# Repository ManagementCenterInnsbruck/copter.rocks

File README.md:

# copter.rocks
Quadcopter Design Contest by MCI &amp; Infineon
This software and hardware is hosted by a cooperation by MCI and Infineon for the "copter.rocks" quadcopter design contest in Austria

More information about the project: https://copter.rocks/

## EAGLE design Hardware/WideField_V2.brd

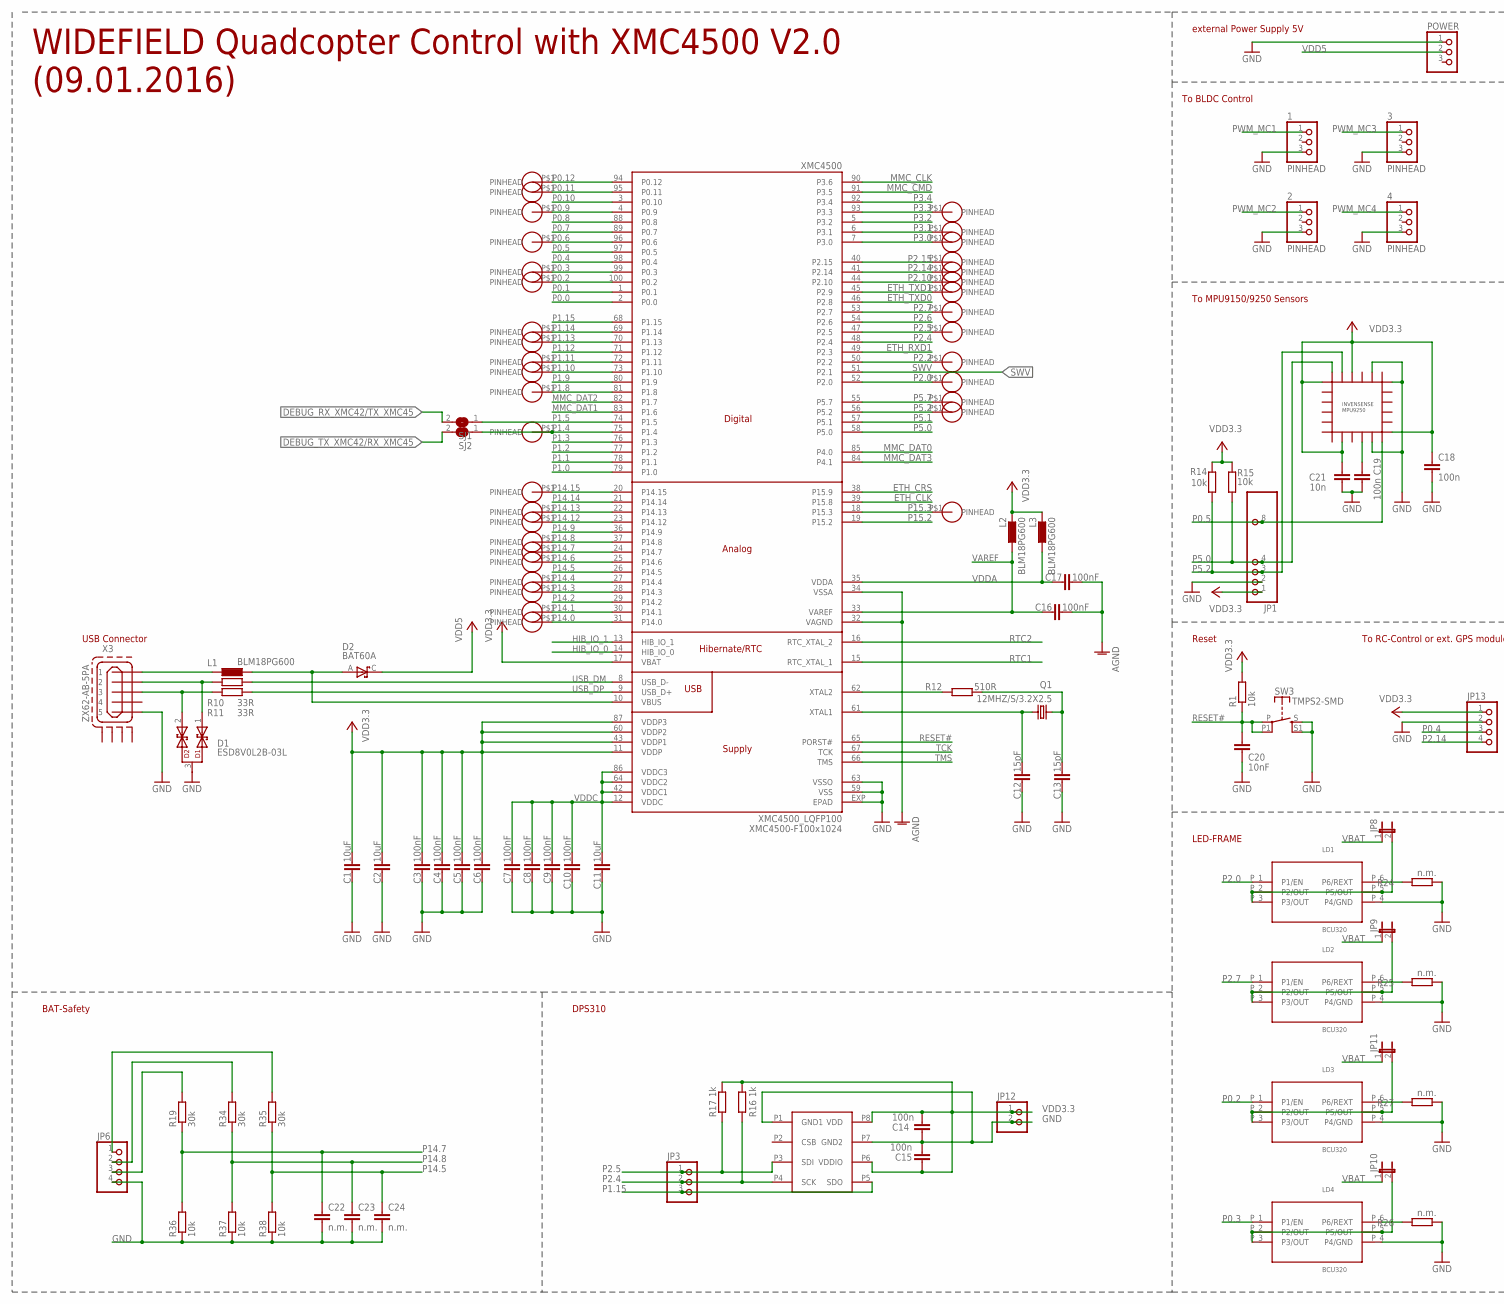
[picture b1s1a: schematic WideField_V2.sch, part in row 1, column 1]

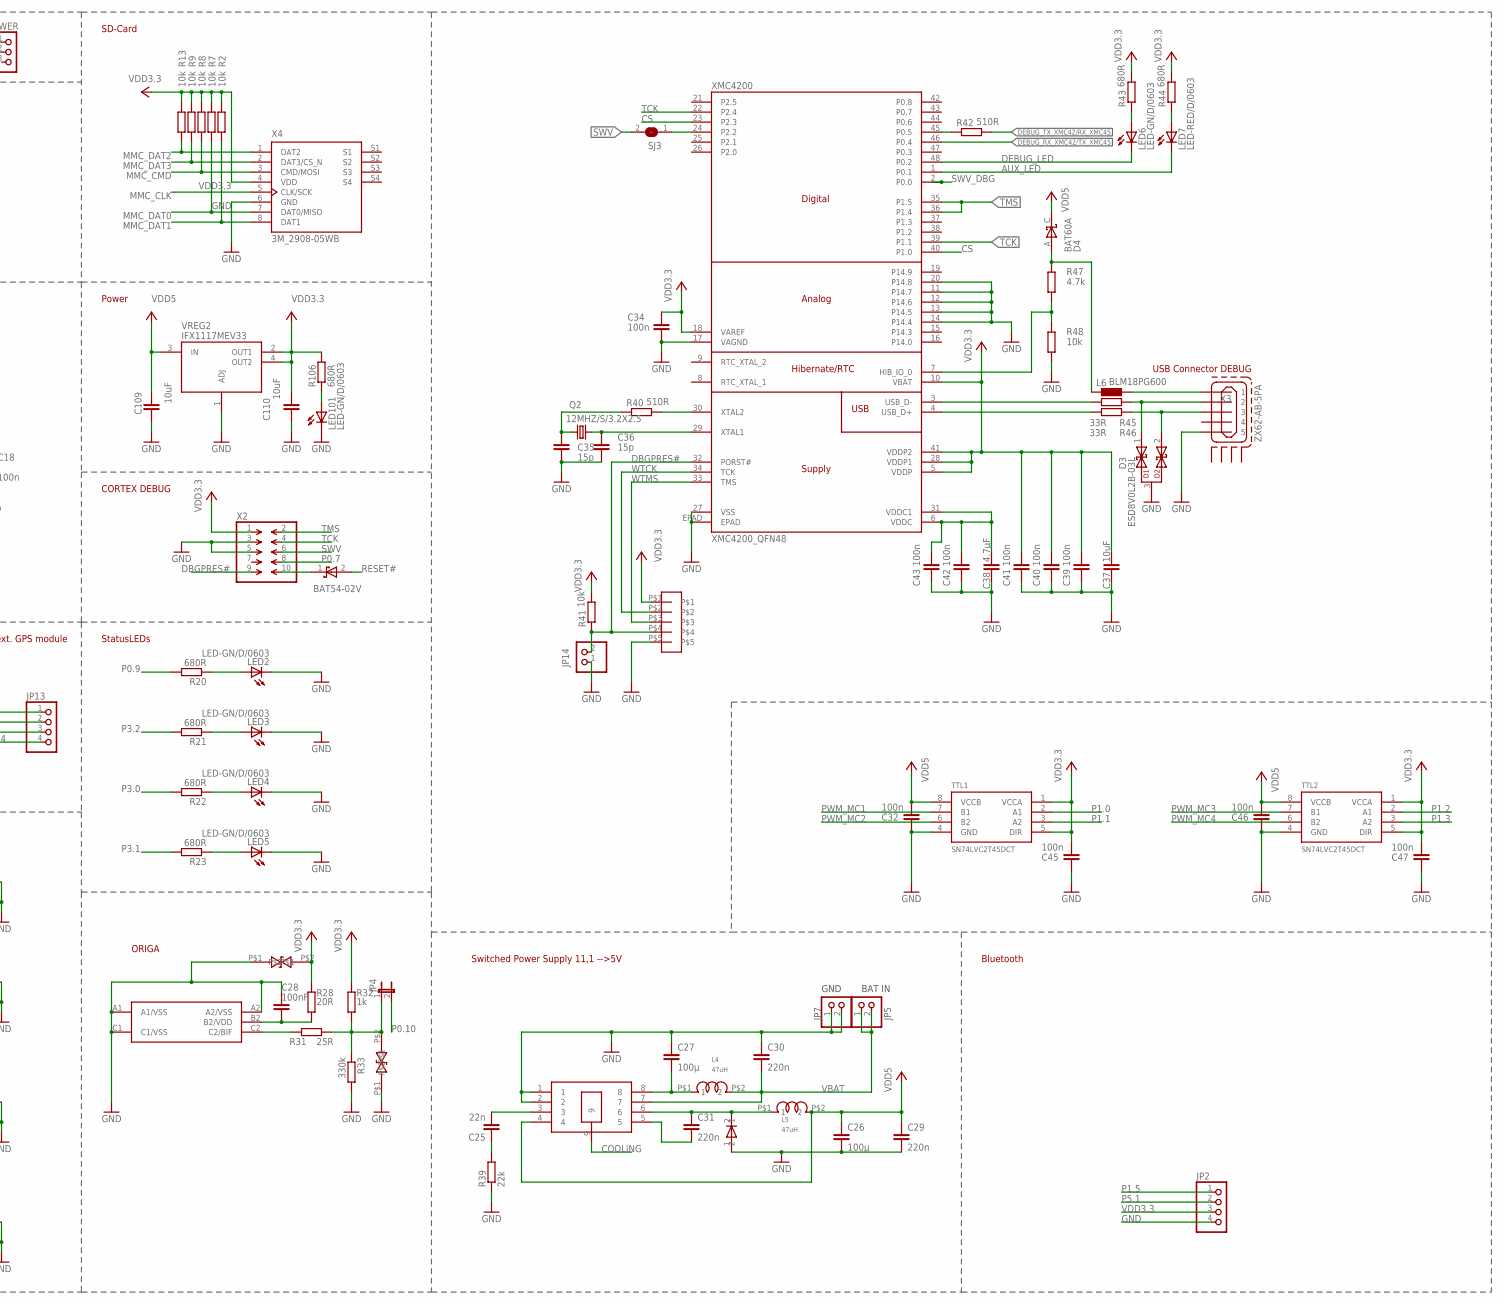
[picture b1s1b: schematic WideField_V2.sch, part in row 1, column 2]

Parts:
1, 2, 3, 4: PINHEAD; 1X03
C1, C2, C11, C37, C109, C110: 10uF; C0805K
C3, C4, C5, C6, C7, C8, C9, C10, C16, C17: 100nF; C0402
C12, C13: 15pF; C0402
C14, C15, C18, C19, C32, C45, C46, C47: 100n; C0603
C20: 10nF; C0603
C21: 10n; C0603
C22, C23, C24: n.m.; C0603K
C25: 22n; C0603
C26, C27: 100µ; C1210K
C28: 100nF; C0603
C29, C30, C31: 220n; C0603K
C34, C39, C40, C41, C42, C43: 100n; C0402
C35, C36: 15p; C0402
C38: 4.7µF; C0805K
D1, D3: ESD8V0L2B-03L; TSLP-3-1
D2, D4: BAT60A; SOD323-R
D5: INF-SOD323_V_1; INF-SOD323_V_1PRIMARY
D6, D7: ESD218-B1-02EL; TSLP-2-20
D8: BAT54-02V; SC79
DPS310: DPS310; LGA8R125P0X4_500X300X120
JP1: PINHD-1X10; 1X10
JP2, JP6, JP13: PINHD-1X4; 1X04
JP3: PINHD-1X3; 1X03
JP4, JP8, JP9, JP10, JP11: JP1E; JP1
JP5, JP7, JP12, JP14: PINHD-1X2; 1X02
L1, L2, L3, L6: BLM18PG600; L1608
L4, L5: 47uH; WE-TPC
LD1, LD2, LD3, LD4: BCU320; SC74
LED2, LED3, LED4, LED5, LED6, LED101: LED-GN/D/0603; CHIPLED_0603
LED7: LED-RED/D/0603; CHIPLED_0603
MPU9250: 9250; QFN3X3-24+
ORIGA: n.m.; WLB-5
POWER: PINHD-1X3; 1X03
Q1, Q2: 12MHZ/S/3.2X2.5; 32X25_4PAD
R1, R14, R15, R36, R37, R38: 10k; R0603
R2, R7, R8, R9, R13, R41, R48: 10k; R0402
R10, R11, R45, R46: 33R; R0402
R12: 510R; R0603
R16, R17, R32: 1k; R0603
R19, R34, R35: 30k; R0603
R20, R21, R22, R23, R106: 680R; R0603
R24, R25, R26, R27: n.m.; R0603
R28: 20R; R0603
R31: 25R; R0603
R33: 330k; R0603
R39: 22k; R0603
R40, R42: 510R; R0402
R43, R44: 680R; R0402
R47: 4.7k; R0402
SJ1, SJ2, SJ3: SJ
SW3: TMPS2-SMD; FSM2JSMA
TTL1, TTL2: SN74LVC2T45DCT; DCT_R-PDSO-G8
U$4: SEGGER.L_100; LOGO_100
U$6, U$7, U$10, U$25, U$26, U$27, U$28, U$29, U$30, U$31, U$35, U$36, U$37, U$38, U$40, U$41, U$42, U$44, U$45, U$47, U$48, U$49, U$52, U$53, U$55, U$57, U$59, U$60, U$62, U$63, U$65, U$67, U$68, U$71, U$74, U$76: PINHEADSMALL1; PINHEADER_SMALL1
U$12: n.m.; PINHEAD_127
USB1, USB2: ZX62-AB-5PA; ZX62-AB-5PA_MICRO-USB
VREG1: IFX-91041-V50; INF-PG-DSO-8-27_N_1PRIMARY
VREG2: IFX1117MEV33; SOT223
X2: FTSH-105-01-F-D-K
X4: 3M_2908-05WB; 3M_MICRO-SD_SLOT
XMC4200: XMC4200_QFN48; QFN-48-7X7
XMC4500: XMC4500_LQFP100; P/PG-LQFP-100-11

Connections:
AGND: C16.2, C17.2, XMC4500.32 (VAGND), XMC4500.34 (VSSA)
AUX_LED: LED7.C, XMC4200.1 (P0.1)
COOLING: VREG1.9
CS: XMC4200.23 (P2.3), XMC4200.40 (P1.0)
DBGPRES#: JP14.2, R41.1, U$12.P$4, X2.9, XMC4200.32 (PORST#)
DEBUG_LED: LED6.C, XMC4200.48 (P0.2)
DEBUG_RX_XMC42/TX_XMC45: SJ1.2, XMC4200.46 (P0.4)
DEBUG_TX_XMC42/RX_XMC45: R42.2, SJ2.2
ETH_CLK: XMC4500.39 (P15.8)
ETH_CRS: XMC4500.38 (P15.9)
ETH_RXD1: XMC4500.49 (P2.3)
ETH_TXD0: XMC4500.46 (P2.8)
ETH_TXD1: U$30.P$1, XMC4500.45 (P2.9)
GND: 1.3, 2.3, 3.3, 4.3, C1.2, C2.2, C3.2, C4.2, C5.2, C6.2, C7.2, C8.2, C9.2, C10.2, C11.2, C12.2, C13.2, C14.2, C15.1, C18.2, C19.1, C20.2, C21.1, C22.2, C23.2, C24.2, C26.2, C27.1, C28.1, C29.2, C30.1, C32.2, C34.2, C35.2, C36.2, C37.2, C38.2, C39.2, C40.2, C41.2, C42.2, C43.2, C45.2, C46.2, C47.2, C109.2, C110.2, D1.3, D3.3, D5.1, D6.P$1, D7.P$1, DPS310.P1 (GND1), DPS310.P7 (GND2), JP1.2, JP2.4, JP6.4, JP7.1, JP7.2, JP12.2, JP13.2, JP14.1, LD1.P_4 (P4/GND), LD2.P_4 (P4/GND), LD3.P_4 (P4/GND), LD4.P_4 (P4/GND), LED2.C, LED3.C, LED4.C, LED5.C, LED101.C, MPU9250.11, MPU9250.18, MPU9250.20, ORIGA.A1 (A1/VSS), ORIGA.A2 (A2/VSS), ORIGA.C1 (C1/VSS), POWER.1, R24.2, R25.2, R26.2, R27.2, R33.2, R36.1, R37.1, R38.1, R39.1, R48.2, SW3.S, SW3.S1 (S), TTL1.4 (GND), TTL2.4 (GND), U$12.P$5, USB1.5, USB2.5, VREG1.1, VREG1.2, VREG2.1 (ADJ), X2.3, X2.5, X4.6 (GND), XMC4200.11 (P14.7), XMC4200.12 (P14.6), XMC4200.13 (P14.5), XMC4200.14 (P14.4), XMC4200.17 (VAGND), XMC4200.20 (P14.8), XMC4200.27 (VSS), XMC4200.EPAD, XMC4500.59 (VSS), XMC4500.63 (VSSO), XMC4500.EXP (EPAD)
HIB_IO_0: XMC4500.14 (HIB_IO_0)
HIB_IO_1: XMC4500.13 (HIB_IO_1)
MMC_CLK: X4.5 (CLK/SCK), XMC4500.90 (P3.6)
MMC_CMD: R8.1, X4.3 (CMD/MOSI), XMC4500.91 (P3.5)
MMC_DAT0: R7.1, X4.7 (DAT0/MISO), XMC4500.85 (P4.0)
MMC_DAT1: R2.1, X4.8 (DAT1), XMC4500.83 (P1.6)
MMC_DAT2: R13.1, X4.1 (DAT2), XMC4500.82 (P1.7)
MMC_DAT3: R9.1, X4.2 (DAT3/CS_N), XMC4500.84 (P4.1)
unnamed: LED2.A, R20.1
unnamed: C38.1, C42.1, C43.1, XMC4200.6 (VDDC), XMC4200.31 (VDDC1)
unnamed: LED3.A, R21.1
unnamed: LED6.A, R43.1
unnamed: LED7.A, R44.1
unnamed: R12.1, XMC4500.62 (XTAL2)
unnamed: C13.1, Q1.3 (2), R12.2
unnamed: C12.1, Q1.1, XMC4500.61 (XTAL1)
unnamed: JP6.1, R35.2
unnamed: C35.1, Q2.1, R40.1
unnamed: L1.2, USB1.1
unnamed: C25.2, VREG1.3
unnamed: D1.1, R10.1, USB1.2
unnamed: C25.1, R39.2
unnamed: LED101.A, R106.1
unnamed: C27.2, L4.P$1 (1), VREG1.8
unnamed: C28.2, ORIGA.B2 (B2/VDD), R28.2
unnamed: JP6.2, R34.2
unnamed: LED4.A, R22.1
unnamed: D2.A, L1.1, XMC4500.10 (VBUS)
unnamed: LED5.A, R23.1
unnamed: ORIGA.C2 (C2/BIF), R31.1
unnamed: LD1.P_6 (P6/REXT), R24.1
unnamed: D6.P$2, JP4.1, R31.2, R32.2, R33.1
unnamed: JP8.2, LD1.P_2 (P2/OUT), LD1.P_3 (P3/OUT), LD1.P_5 (P5/OUT)
unnamed: LD2.P_6 (P6/REXT), R25.1
unnamed: JP9.2, LD2.P_2 (P2/OUT), LD2.P_3 (P3/OUT), LD2.P_5 (P5/OUT)
unnamed: LD4.P_6 (P6/REXT), R26.1
unnamed: JP10.2, LD4.P_2 (P2/OUT), LD4.P_3 (P3/OUT), LD4.P_5 (P5/OUT)
unnamed: LD3.P_6 (P6/REXT), R27.1
unnamed: JP11.2, LD3.P_2 (P2/OUT), LD3.P_3 (P3/OUT), LD3.P_5 (P5/OUT)
unnamed: JP6.3, R19.2
unnamed: D1.2, R11.1, USB1.3
unnamed: C31.2, VREG1.5
unnamed: L6.2, USB2.1
unnamed: C31.1, D5.2, L5.P$1 (1), VREG1.6
unnamed: R40.2, XMC4200.30 (XTAL2)
unnamed: C36.1, Q2.3 (2), XMC4200.29 (XTAL1)
unnamed: C19.2, MPU9250.10
unnamed: D8.1 (C), X2.10
unnamed: D3.1, R45.1, USB2.2
unnamed: D3.2, R46.1, USB2.3
unnamed: D4.A, L6.1, R47.1
unnamed: R42.1, XMC4200.45 (P0.5)
unnamed: R47.2, R48.1, XMC4200.7 (HIB_IO_0)
P0.0: XMC4500.2 (P0.0)
P0.1: XMC4500.1 (P0.1)
P0.2: LD3.P_1 (P1/EN), U$67.P$1, XMC4500.100 (P0.2)
P0.3: LD4.P_1 (P1/EN), U$68.P$1, XMC4500.99 (P0.3)
P0.4: JP13.3, XMC4500.98 (P0.4)
P0.5: JP1.8, MPU9250.12, XMC4500.97 (P0.5)
P0.6: U$71.P$1, XMC4500.96 (P0.6)
P0.7: X2.8, XMC4500.89 (P0.7)
P0.8: XMC4500.88 (P0.8)
P0.9: R20.2, U$74.P$1, XMC4500.4 (P0.9)
P0.10: JP4.2, XMC4500.3 (P0.10)
P0.11: U$76.P$1, XMC4500.95 (P0.11)
P0.12: U$7.P$1, XMC4500.94 (P0.12)
P1.0: TTL1.2 (A1), XMC4500.79 (P1.0)
P1.1: TTL1.3 (A2), XMC4500.78 (P1.1)
P1.2: TTL2.2 (A1), XMC4500.77 (P1.2)
P1.3: TTL2.3 (A2), XMC4500.76 (P1.3)
P1.4: SJ2.1, U$40.P$1, XMC4500.75 (P1.4)
P1.5: JP2.1, SJ1.1, XMC4500.74 (P1.5)
P1.8: U$57.P$1, XMC4500.81 (P1.8)
P1.9: XMC4500.80 (P1.9)
P1.10: U$59.P$1, XMC4500.73 (P1.10)
P1.11: U$60.P$1, XMC4500.72 (P1.11)
P1.12: XMC4500.71 (P1.12)
P1.13: U$62.P$1, XMC4500.70 (P1.13)
P1.14: U$63.P$1, XMC4500.69 (P1.14)
P1.15: DPS310.P5 (SDO), JP3.3, XMC4500.68 (P1.15)
P2.0: LD1.P_1 (P1/EN), U$35.P$1, XMC4500.52 (P2.0)
P2.2: U$65.P$1, XMC4500.50 (P2.2)
P2.4: DPS310.P4 (SCK), JP3.2, R16.2, XMC4500.48 (P2.4)
P2.5: DPS310.P3 (SDI), JP3.1, R17.2, U$31.P$1, XMC4500.47 (P2.5)
P2.6: XMC4500.54 (P2.6)
P2.7: LD2.P_1 (P1/EN), U$29.P$1, XMC4500.53 (P2.7)
P2.10: U$28.P$1, XMC4500.44 (P2.10)
P2.14: JP13.4, U$27.P$1, XMC4500.41 (P2.14)
P2.15: U$26.P$1, XMC4500.40 (P2.15)
P3.0: R22.2, U$25.P$1, XMC4500.7 (P3.0)
P3.1: R23.2, U$10.P$1, XMC4500.6 (P3.1)
P3.2: R21.2, XMC4500.5 (P3.2)
P3.3: U$6.P$1, XMC4500.93 (P3.3)
P3.4: XMC4500.92 (P3.4)
P5.0: JP1.4, MPU9250.24, R15.1, XMC4500.58 (P5.0)
P5.1: JP2.2, XMC4500.57 (P5.1)
P5.2: JP1.3, MPU9250.23, R14.1, U$37.P$1, XMC4500.56 (P5.2)
P5.7: U$36.P$1, XMC4500.55 (P5.7)
P14.0: U$41.P$1, XMC4500.31 (P14.0)
P14.1: U$42.P$1, XMC4500.30 (P14.1)
P14.2: XMC4500.29 (P14.2)
P14.3: U$44.P$1, XMC4500.28 (P14.3)
P14.4: U$45.P$1, XMC4500.27 (P14.4)
P14.5: C24.1, R35.1, R38.2, XMC4500.26 (P14.5)
P14.6: U$47.P$1, XMC4500.25 (P14.6)
P14.7: C22.1, R19.1, R36.2, U$48.P$1, XMC4500.24 (P14.7)
P14.8: C23.1, R34.1, R37.2, U$49.P$1, XMC4500.37 (P14.8)
P14.9: XMC4500.36 (P14.9)
P14.12: U$52.P$1, XMC4500.23 (P14.12)
P14.13: U$53.P$1, XMC4500.22 (P14.13)
P14.14: XMC4500.21 (P14.14)
P14.15: U$55.P$1, XMC4500.20 (P14.15)
P15.2: XMC4500.19 (P15.2)
P15.3: U$38.P$1, XMC4500.18 (P15.3)
PWM_MC1: 1.1, TTL1.7 (B1)
PWM_MC2: 2.1, TTL1.6 (B2)
PWM_MC3: 3.1, TTL2.7 (B1)
PWM_MC4: 4.1, TTL2.6 (B2)
RESET#: C20.1, D8.2 (A), R1.1, SW3.P, SW3.P1, XMC4500.65 (PORST#)
RTC1: XMC4500.15 (RTC_XTAL_1)
RTC2: XMC4500.16 (RTC_XTAL_2)
SWV: SJ3.2, X2.6, XMC4500.51 (P2.1)
SWV_DBG: SJ3.1, XMC4200.2 (P0.0), XMC4200.24 (P2.2)
TCK: X2.4, XMC4200.22 (P2.4), XMC4200.39 (P1.1), XMC4500.67 (TCK)
TMS: X2.2, XMC4200.35 (P1.5), XMC4200.36 (P1.4), XMC4500.66 (TMS)
USB_DM: R10.2, XMC4500.8 (USB_D-)
USB_DM1: R45.2, XMC4200.3 (USB_D-)
USB_DP: R11.2, XMC4500.9 (USB_D+)
USB_DP1: R46.2, XMC4200.4 (USB_D+)
VAREF: C16.1, L2.1, XMC4500.33 (VAREF)
VBAT: C30.2, JP5.1, JP5.2, JP8.1, JP9.1, JP10.1, JP11.1, L4.P$2 (2), VREG1.7
VDD3.3: C1.1, C2.1, C3.1, C4.1, C5.1, C6.1, C14.1, C15.2, C18.1, C21.2, C34.1, C37.1, C39.1, C40.1, C41.1, C45.1, C47.1, C110.1, D7.P$2, DPS310.P6 (VDDIO), DPS310.P8 (VDD), JP1.1, JP2.3, JP12.1, JP13.1, L2.2, L3.2, MPU9250.1, MPU9250.8, MPU9250.13, MPU9250.22, R1.2, R2.2, R7.2, R8.2, R9.2, R13.2, R14.2, R15.2, R16.1, R17.1, R28.1, R32.1, R41.2, R43.2, R44.2, R106.2, TTL1.1 (VCCA), TTL1.5 (DIR), TTL2.1 (VCCA), TTL2.5 (DIR), U$12.P$1, VREG2.2 (OUT1), VREG2.4 (OUT2), X2.1, X4.4 (VDD), XMC4200.5 (VDDP), XMC4200.10 (VBAT), XMC4200.18 (VAREF), XMC4200.28 (VDDP1), XMC4200.41 (VDDP2), XMC4500.11 (VDDP), XMC4500.17 (VBAT), XMC4500.43 (VDDP1), XMC4500.60 (VDDP2), XMC4500.87 (VDDP3)
VDD5: C26.1, C29.1, C32.1, C46.1, C109.1, D2.C, D4.C, L5.P$2 (2), POWER.2, TTL1.8 (VCCB), TTL2.8 (VCCB), VREG1.4, VREG2.3 (IN)
VDDA: C17.1, L3.1, XMC4500.35 (VDDA)
VDDC: C7.1, C8.1, C9.1, C10.1, C11.1, XMC4500.12 (VDDC), XMC4500.42 (VDDC1), XMC4500.64 (VDDC2), XMC4500.86 (VDDC3)
WTCK: U$12.P$2, XMC4200.34 (TCK)
WTMS: U$12.P$3, XMC4200.33 (TMS)

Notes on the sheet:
USB Connector
Reset
WIDEFIELD Quadcopter Control with XMC4500 V2.0 (09.01.2016)
XMC4500-F100x1024
To RC-Control or ext. GPS module
To MPU9150/9250 Sensors
To BLDC Control
external Power Supply 5V
Power
SD-Card
Bluetooth
StatusLEDs
LED-FRAME
DPS310
ORIGA
Switched Power Supply 11,1 -->5V
CORTEX DEBUG
BAT IN
GND
BAT-Safety
USB Connector DEBUG

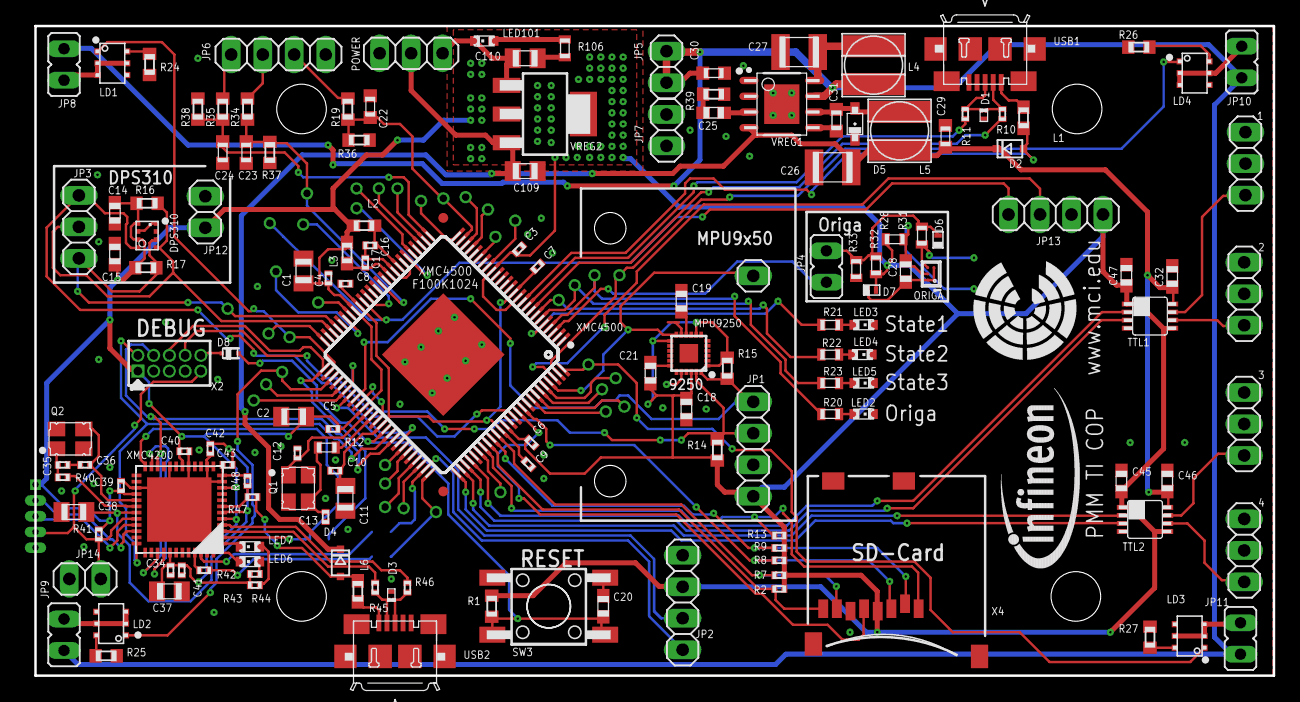
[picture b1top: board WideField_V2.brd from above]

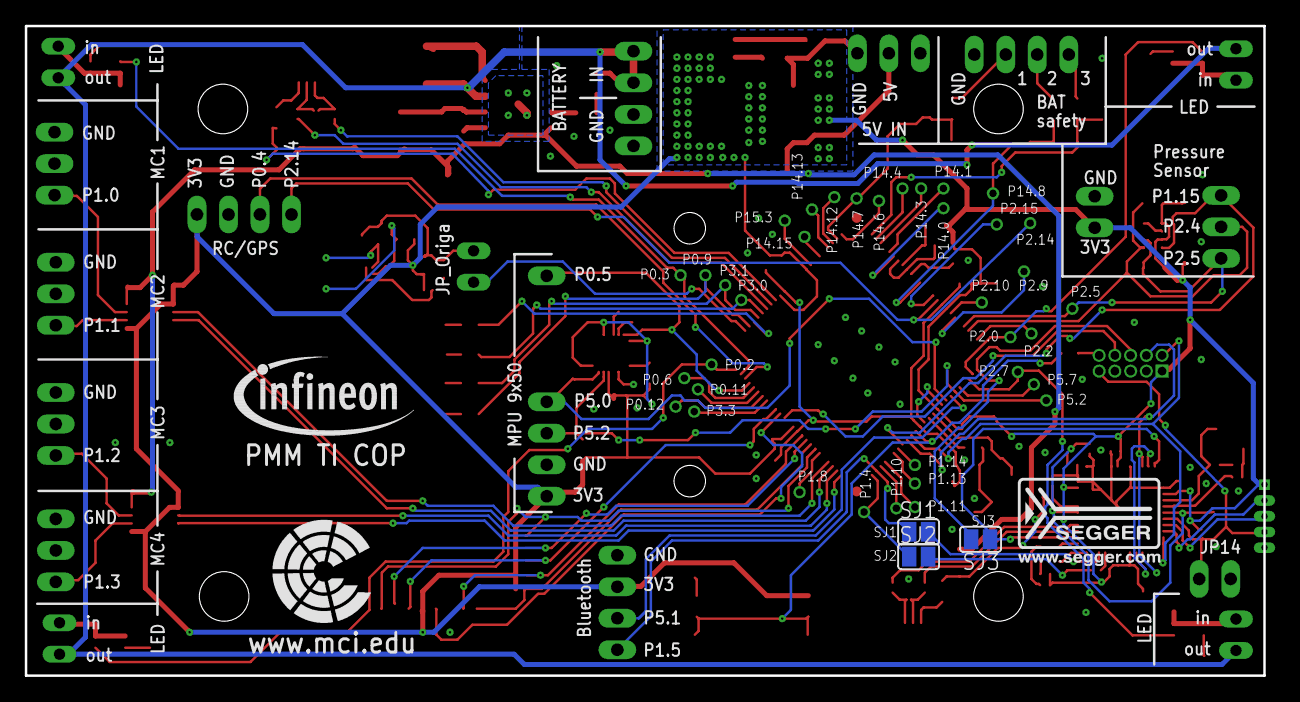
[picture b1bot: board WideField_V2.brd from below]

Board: 2 copper layers, 99.9 x 52.4 mm, 190 parts (3 on the bottom side), 131 nets.

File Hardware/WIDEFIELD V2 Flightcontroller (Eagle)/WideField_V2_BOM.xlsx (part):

Infineon Widefield V2 PCB BOM
 | NAME | VALUE | PACKAGE |  | DESCRIPTION | TOLERANCE | VOLTAGE | ADD. INFORMATION | PROVIDED BY | Farnell Code | RS-Online Code
 | 1 | PINHEAD | PINHD-1X3 | 1X03 | PIN HEADER |  |  |  |  |  | 828-1585
 | 2 | PINHEAD | PINHD-1X3 | 1X03 | PIN HEADER |  |  |  |  |  | 828-1585
 | 3 | PINHEAD | PINHD-1X3 | 1X03 | PIN HEADER |  |  |  |  |  | 828-1585
 | 4 | PINHEAD | PINHD-1X3 | 1X03 | PIN HEADER |  |  |  |  |  | 828-1585
 | C1 | 10uF | C-EUC0805K | C0805K | CAPACITOR, European symbol | 0.1 | 16V | X5R |  | 1288204
 | C2 | 10uF | C-EUC0805K | C0805K | CAPACITOR, European symbol | 0.1 | 16V | X5R |  | 1288204
 | C3 | 100nF | C-EUC0402 | C0402 | CAPACITOR, European symbol | 0.1 | 10V | X7R |  | 1828860
 | C4 | 100nF | C-EUC0402 | C0402 | CAPACITOR, European symbol | 0.1 | 10V | X7R |  | 1828860
 | C5 | 100nF | C-EUC0402 | C0402 | CAPACITOR, European symbol | 0.1 | 10V | X7R |  | 1828860
 | C6 | 100nF | C-EUC0402 | C0402 | CAPACITOR, European symbol | 0.1 | 10V | X7R |  | 1828860
 | C7 | 100nF | C-EUC0402 | C0402 | CAPACITOR, European symbol | 0.1 | 10V | X7R |  | 1828860
 | C8 | 100nF | C-EUC0402 | C0402 | CAPACITOR, European symbol | 0.1 | 10V | X7R |  | 1828860
 | C9 | 100nF | C-EUC0402 | C0402 | CAPACITOR, European symbol | 0.1 | 10V | X7R |  | 1828860
 | C10 | 100nF | C-EUC0402 | C0402 | CAPACITOR, European symbol | 0.1 | 10V | X7R |  | 1828860
 | C11 | 10uF | C-EUC0805K | C0805K | CAPACITOR, European symbol | 0.1 | 16V | X5R |  | 1288204
 | C12 | 15pF | C-EUC0402 | C0402 | CAPACITOR, European symbol | 0.05 | 50V | C0G/NP0 |  | 1758945
 | C13 | 15pF | C-EUC0402 | C0402 | CAPACITOR, European symbol | 0.05 | 50V | C0G/NP0 |  | 1758945
 | C14 | 100n | C-EUC0603 | C0603 | CAPACITOR, European symbol | 0.1 | 10V | X7R |  | 2112833
 | C15 | 100n | C-EUC0603 | C0603 | CAPACITOR, European symbol | 0.1 | 10V | X7R |  | 2112833
 | C16 | 100nF | C-EUC0402 | C0402 | CAPACITOR, European symbol | 0.1 | 10V | X7R |  | 1828860
 | C17 | 100nF | C-EUC0402 | C0402 | CAPACITOR, European symbol | 0.1 | 10V | X7R |  | 1828860
 | C18 | 100n | C-EUC0603 | C0603 | CAPACITOR, European symbol | 0.1 | 10V | X7R |  | 2112833
 | C19 | 100n | C-EUC0603 | C0603 | CAPACITOR, European symbol | 0.1 | 10V | X7R |  | 2112833
 | C20 | 10nF | C-EUC0603 | C0603 | CAPACITOR, European symbol | 0.1 | 50V | X7R |  | 9406182
 | C21 | 10n | C-EUC0603 | C0603 | CAPACITOR, European symbol | 0.1 | 50V | X7R |  | 9406182
 | C22 | n.m. | C-EUC0603K | C0603K | CAPACITOR, European symbol
 | C23 | n.m. | C-EUC0603K | C0603K | CAPACITOR, European symbol
 | C24 | n.m. | C-EUC0603K | C0603K | CAPACITOR, European symbol
 | C25 | 22n | C-EUC0603 | C0603 | CAPACITOR, European symbol | 0.1 | 50V | X7R |  | 1414625
 | C26 | 100µ | C-EUC1210K | C1210K | CAPACITOR, European symbol | 0.2 | 16V | X5R |  | 2309033
 | C27 | 100µ | C-EUC1210K | C1210K | CAPACITOR, European symbol | 0.2 | 16V | X5R |  | 2309033
 | C28 | 100nF | C-EUC0603 | C0603 | CAPACITOR, European symbol | 0.1 | 10V | X7R |  | 2112833
 | C29 | 220n | C-EUC0603K | C0603K | CAPACITOR, European symbol | 0.1 | 16V | X7R |  | 1414032
 | C30 | 220n | C-EUC0603K | C0603K | CAPACITOR, European symbol | 0.1 | 16V | X7R |  | 1414032
 | C31 | 220n | C-EUC0603K | C0603K | CAPACITOR, European symbol | 0.1 | 16V | X7R |  | 1414032
 | C32 | 100n | C-EUC0603 | C0603 | CAPACITOR, European symbol | 0.1 | 10V | X7R |  | 2112833
 | C34 | 100n | C-EUC0402 | C0402 | CAPACITOR, European symbol | 0.1 | 10V | X7R |  | 1828860
 | C35 | 15p | C-EUC0402 | C0402 | CAPACITOR, European symbol | 0.05 | 50V | C0G/NP0 |  | 1758945
 | C36 | 15p | C-EUC0402 | C0402 | CAPACITOR, European symbol | 0.05 | 50V | C0G/NP0 |  | 1758945
 | C37 | 10uF | C-EUC0805K | C0805K | CAPACITOR, European symbol | 0.1 | 16V | X5R |  | 1288204
 | C38 | 4.7µF | C-EUC0805K | C0805K | CAPACITOR, European symbol | 0.1 | 16V | X7R |  | 1657937
 | C39 | 100n | C-EUC0402 | C0402 | CAPACITOR, European symbol | 0.1 | 10V | X7R |  | 1828860
 | C40 | 100n | C-EUC0402 | C0402 | CAPACITOR, European symbol | 0.1 | 10V | X7R |  | 1828860
 | C41 | 100n | C-EUC0402 | C0402 | CAPACITOR, European symbol | 0.1 | 10V | X7R |  | 1828860
 | C42 | 100n | C-EUC0402 | C0402 | CAPACITOR, European symbol | 0.1 | 10V | X7R |  | 1828860
 | C43 | 100n | C-EUC0402 | C0402 | CAPACITOR, European symbol | 0.1 | 10V | X7R |  | 1828860
 | C45 | 100n | C-EUC0603 | C0603 | CAPACITOR, European symbol | 0.1 | 10V | X7R |  | 2112833
 | C46 | 100n | C-EUC0603 | C0603 | CAPACITOR, European symbol | 0.1 | 10V | X7R |  | 2112833
 | C47 | 100n | C-EUC0603 | C0603 | CAPACITOR, European symbol | 0.1 | 10V | X7R |  | 2112833
 | C109 | 10uF | C-EUC0805K | C0805K | CAPACITOR, European symbol | 0.1 | 16V | X5R |  | 1288204
 | C110 | 10uF | C-EUC0805K | C0805K | CAPACITOR, European symbol | 0.1 | 16V | X5R |  | 1288204
 | D1 | ESD8V0L2B-03L | ESD8V0L2B-03L | TSLP-3-1 | Diode |  |  |  | INFINEON
 | D2 | BAT60A | BAT60 | SOD323-R | Diode |  |  |  | INFINEON
 | D3 | ESD8V0L2B-03L | ESD8V0L2B-03L | TSLP-3-1 | Diode |  |  |  | INFINEON
 | D4 | BAT60A | BAT60 | SOD323-R | Diode |  |  |  | INFINEON
 | D5 | INF-SOD323_V_1 | INF-SOD323_V_1 | INF-SOD323_V_1PRIMARY | Diode |  |  |  | INFINEON
 | D6 | ESD218-B1-02EL | ESD218-B1-02EL | TSLP-2-20 | Diode |  |  |  | INFINEON
 | D7 | ESD218-B1-02EL | ESD218-B1-02EL | TSLP-2-20 | Diode |  |  |  | INFINEON
 | DPS310 | DPS310 | DPS310DRUCKSENSOR | LGA8R125P0X4_500X300X120 |  |  |  |  | INFINEON
 | JP1 | n.m. | PINHD-1X10 | 1X10 | PIN HEADER
 | JP2 |  | PINHD-1X4 | 1X04 | PIN HEADER |  |  | 4 Pins needed from header |  |  | 763-6750
 | JP3 | n.m. | PINHD-1X3 | 1X03 | PIN HEADER
 | JP4 | n.m. | JP1E | JP1 | JUMPER
 | JP5 |  | PINHD-1X2 | 1X02 | PIN HEADER |  |  | 2 Pins needed from header |  |  | 763-6750
 | JP6 |  | PINHD-1X4 | 1X04 | PIN HEADER |  |  | 4 Pins needed from header |  |  | 763-6750
 | JP7 |  | PINHD-1X2 | 1X02 | PIN HEADER |  |  | 2 Pins needed from header |  |  | 763-6750
 | JP8 |  | JP1E | JP1 | JUMPER |  |  |  |  |  | 763-6750
 | JP9 |  | JP1E | JP1 | JUMPER |  |  |  |  |  | 763-6750
 | JP10 |  | JP1E | JP1 | JUMPER |  |  |  |  |  | 763-6750
 | JP11 |  | JP1E | JP1 | JUMPER |  |  |  |  |  | 763-6750
 | JP12 | n.m. | PINHD-1X2 | 1X02 | PIN HEADER
 | JP13 |  | PINHD-1X4 | 1X04 | PIN HEADER |  |  | 4 Pins needed from header |  |  | 763-6750
 | JP14 |  | PINHD-1X2 | 1X02 | PIN HEADER |  |  | 2 Pins needed from header |  |  | 763-6750
 | L1 | BLM18PG600 | L_EU_L0603 | L1608 | INDUCTANCE |  |  |  | INFINEON
 | L2 | BLM18PG600 | L_EU_L0603 | L1608 | INDUCTANCE |  |  |  | INFINEON
 | L3 | BLM18PG600 | L_EU_L0603 | L1608 | INDUCTANCE |  |  |  | INFINEON
 | L4 | 47uH | WUERTH47UHIND | WE-TPC | INDUCTANCE |  |  |  | INFINEON
 | L5 | 47uH | WUERTH47UHIND | WE-TPC | INDUCTANCE |  |  |  | INFINEON
 | L6 | BLM18PG600 | L_EU_L0603 | L1608 | INDUCTANCE |  |  |  | INFINEON
 | LD1 | BCU320 | BCU320 | SC74 |  |  |  |  | INFINEON
 | LD2 | BCU320 | BCU320 | SC74 |  |  |  |  | INFINEON
 | LD3 | BCU320 | BCU320 | SC74 |  |  |  |  | INFINEON
 | LD4 | BCU320 | BCU320 | SC74 |  |  |  |  | INFINEON
 | LED2 | LED-GN/D/0603 | LEDCHIPLED_0603 | CHIPLED_0603 | LED |  |  |  |  | 2112121
 | LED3 | LED-GN/D/0603 | LEDCHIPLED_0603 | CHIPLED_0603 | LED |  |  |  |  | 2112121
 | LED4 | LED-GN/D/0603 | LEDCHIPLED_0603 | CHIPLED_0603 | LED |  |  |  |  | 2112121
 | LED5 | LED-GN/D/0603 | LEDCHIPLED_0603 | CHIPLED_0603 | LED |  |  |  |  | 2112121
 | LED6 | LED-GN/D/0603 | LEDCHIPLED_0603 | CHIPLED_0603 | LED |  |  |  |  | 2112121
 | LED7 | LED-RED/D/0603 | LEDCHIPLED_0603 | CHIPLED_0603 | LED |  |  |  |  | 2112124
 | LED101 | LED-GN/D/0603 | LEDCHIPLED_0603 | CHIPLED_0603 | LED |  |  |  |  | 2112121
 | MPU9250 | 9250 | INVENSENSE9250IHERBY | QFN3X3-24+ | INVENSENSE MPU 9250 |  |  |  | INFINEON
 | ORIGA | n.m. | ORIGA2L | WLB-5
 | POWER |  | PINHD-1X3 | 1X03 | PIN HEADER |  |  |  |  |  | 828-1585
 | Q1 | 12MHZ/S/3.2X2.5 | NX3225_2 | 32X25_4PAD | CRYSTAL |  |  |  |  | 2308707
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
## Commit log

2016-07-14 added files
    README
    LICENSE
    Simulations
    Software
    hardware
2016-07-14 folder updated
2016-09-15 added new Software Release
    - DAVE4 Software version
    - ESC calibration Software
2016-09-19 unpacked Flightcontroller .zip file
    unpacked Flightcontroller .zip file
2016-09-19 updated readme.me
    updated readme.me
2016-09-19 Update README.md
    http -> https
2016-09-19 Update GetAngles for Kalman Filter
    GetAngles now returns the Yawrate (rate of change of the heading angle) for both sensor fusion algorithms.
2016-09-19 removed Flightcontroller.zip, new MPU9250.c file
2016-09-21 added files for design contest in China
    DAVE3 and DAVE4 PWM Flightcontroller version
2016-09-22 Re-Enabling USB debugging support
    It seems that you wanted to cleanup the mess in main.c , so perhaps this is the wrong way to do it. Feel free to do it differently.
2016-10-28 Motor Orientation
